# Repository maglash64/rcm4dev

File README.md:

# RCM4DEV
A Raspberry Pi CM4 Dev Board with HDMI outputs, 4 lane MIPI DSI output for 10.1 inch LCD panel with CTP touch, 4 lane MIPI CSI for camera and USB type-C.
Terminal Block for power in 6 - 17V DC.

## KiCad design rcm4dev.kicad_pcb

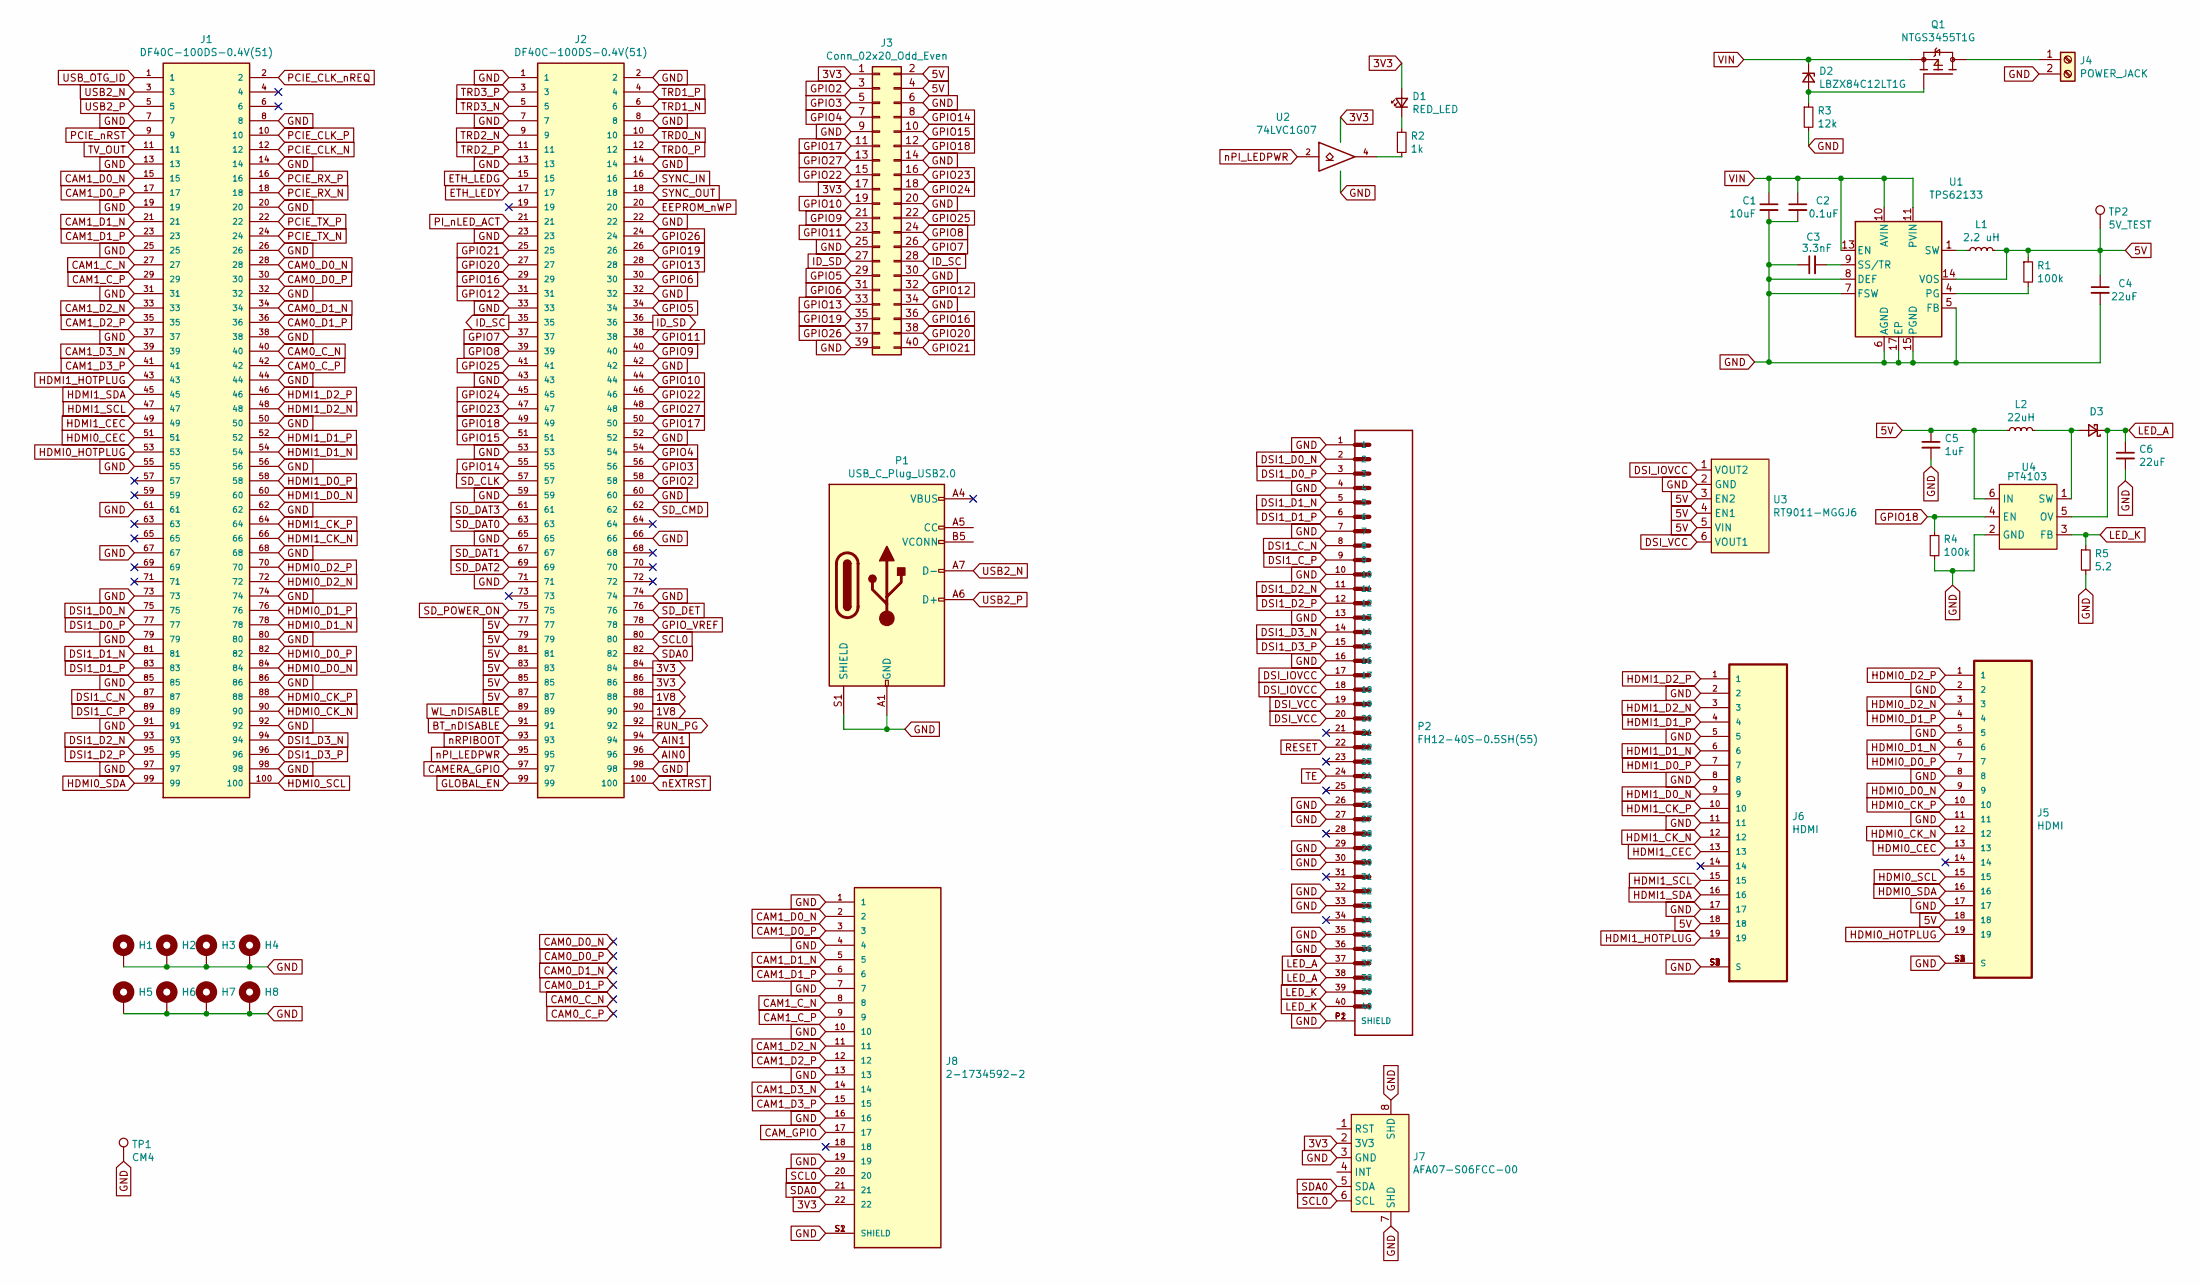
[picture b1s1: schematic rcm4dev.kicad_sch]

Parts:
C1: 10uF; C_1210_3225Metric
C2: 0.1uF; C_0603_1608Metric
C3: 3.3nF; C_0603_1608Metric
C4: 22uF; C_0805_2012Metric
C5: 1uF; C_0603_1608Metric
C6: 22uF; C_0603_1608Metric
D1: RED_LED; LED_0805_2012Metric
D2: LBZX84C12LT1G; SOT-23
D3: D_1206_3216Metric
H1, H2, H3, H4, H5, H6, H7, H8: MountingHole_Pad; MountingHole_2.7mm_M2.5_Pad_Via
J1, J2: DF40C-100DS-0.4V(51); HRS_DF40C-100DS-0.4V(51)
J3: Conn_02x20_Odd_Even; PinHeader_2x20_P2.54mm_Vertical
J4: POWER_JACK; TerminalBlock_Phoenix_MKDS-3-2-5.08_1x02_P5.08mm_Horizontal
J5, J6: HDMI; TE_1827059-3; PARTREV E
J7: AFA07-S06FCC-00
J8: 2-1734592-2; TE_2-1734592-2; PARTREV C
L1: 2.2 uH; L_Vishay_IFSC-1515AH_4x4x1.8mm
L2: 22uH; L_1210_3225Metric
P1: USB_C_Plug_USB2.0; USB_C_Receptacle_HRO_TYPE-C-31-M-12
P2: FH12-40S-0.5SH(55); HRS_FH12-40S-0.5SH(55)
Q1: NTGS3455T1G; SOP95P275X110-6N; PARTREV P
R1: 100k; R_1206_3216Metric
R2: 1k; R_1206_3216Metric
R3: 12k; R_1206_3216Metric
R4: 100k; R_0603_1608Metric
R5: 5.2; R_0603_1608Metric
TP1: CM4; TestPoint_Pad_1.0x1.0mm
TP2: 5V_TEST; TestPoint_Pad_D1.5mm
U1: TPS62133; VQFN-16-1EP_3x3mm_P0.5mm_EP1.68x1.68mm_ThermalVias
U2: 74LVC1G07; SOT-353_SC-70-5
U3: RT9011-MGGJ6; TSOT-23-6
U4: PT4103; TSOT-23-6

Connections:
1V8: J2.88, J2.90
3V3: D1.2 (A), J2.84, J2.86, J3.1, J3.17, J7.2 (3V3), J8.22, U2.5 (VCC)
5V: C4.1, C5.1, J2.77, J2.79, J2.81, J2.83, J2.85, J2.87, J3.2, J3.4, J5.18, J6.18, L1.2, L2.1, R1.1, TP2.1, U1.14 (VOS), U3.3 (EN2), U3.4 (EN1), U3.5 (VIN), U4.6 (IN)
AIN0: J2.96
AIN1: J2.94
BT_nDISABLE: J2.91
CAM0_C_N: J1.40
CAM0_C_P: J1.42
CAM0_D0_N: J1.28
CAM0_D0_P: J1.30
CAM0_D1_N: J1.34
CAM0_D1_P: J1.36
CAM1_C_N: J1.27, J8.8
CAM1_C_P: J1.29, J8.9
CAM1_D0_N: J1.15, J8.2
CAM1_D0_P: J1.17, J8.3
CAM1_D1_N: J1.21, J8.5
CAM1_D1_P: J1.23, J8.6
CAM1_D2_N: J1.33, J8.11
CAM1_D2_P: J1.35, J8.12
CAM1_D3_N: J1.39, J8.14
CAM1_D3_P: J1.41, J8.15
CAMERA_GPIO: J2.97
CAM_GPIO: J8.17
DSI1_C_N: J1.87, P2.8
DSI1_C_P: J1.89, P2.9
DSI1_D0_N: J1.75, P2.2
DSI1_D0_P: J1.77, P2.3
DSI1_D1_N: J1.81, P2.5
DSI1_D1_P: J1.83, P2.6
DSI1_D2_N: J1.93, P2.11
DSI1_D2_P: J1.95, P2.12
DSI1_D3_N: J1.94, P2.14
DSI1_D3_P: J1.96, P2.15
DSI_IOVCC: P2.17, P2.18, U3.1 (VOUT2)
DSI_VCC: P2.19, P2.20, U3.6 (VOUT1)
EEPROM_nWP: J2.20
ETH_LEDG: J2.15
ETH_LEDY: J2.17
GLOBAL_EN: J2.99
GND: C1.2, C2.2, C3.1, C4.2, C5.2, C6.2, H1.1, H2.1, H3.1, H4.1, H5.1, H6.1, H7.1, H8.1, J1.7, J1.8, J1.13, J1.14, J1.19, J1.20, J1.25, J1.26, J1.31, J1.32, J1.37, J1.38, J1.44, J1.50, J1.55, J1.56, J1.61, J1.62, J1.67, J1.68, J1.73, J1.74, J1.79, J1.80, J1.85, J1.86, J1.91, J1.92, J1.97, J1.98, J2.1, J2.2, J2.7, J2.8, J2.13, J2.14, J2.22, J2.23, J2.32, J2.33, J2.42, J2.43, J2.52, J2.53, J2.59, J2.60, J2.65, J2.66, J2.71, J2.74, J2.98, J3.6, J3.9, J3.14, J3.20, J3.25, J3.30, J3.34, J3.39, J4.2, J5.2, J5.5, J5.8, J5.11, J5.17, J5.S1 (S), J5.S2 (S), J5.S3 (S), J5.S4 (S), J6.2, J6.5, J6.8, J6.11, J6.17, J6.S1 (S), J6.S2 (S), J6.S3 (S), J6.S4 (S), J7.3 (GND), J7.7 (SHD), J7.8 (SHD), J8.1, J8.4, J8.7, J8.10, J8.13, J8.16, J8.19, J8.S1 (SHIELD), J8.S2 (SHIELD), P1.A1 (GND), P1.A12 (GND), P1.B1 (GND), P1.B12 (GND), P1.S1 (SHIELD), P2.1, P2.4, P2.7, P2.10, P2.13, P2.16, P2.26, P2.27, P2.29, P2.30, P2.32, P2.33, P2.35, P2.36, P2.P1 (SHIELD), P2.P2 (SHIELD), R3.2, R4.2, R5.2, TP1.1, U1.5 (FB), U1.6 (AGND), U1.7 (FSW), U1.8 (DEF), U1.15 (PGND), U1.16 (PGND), U1.17 (EP), U2.3 (GND), U3.2 (GND), U4.2 (GND)
GPIO2: J2.58, J3.3
GPIO3: J2.56, J3.5
GPIO4: J2.54, J3.7
GPIO5: J2.34, J3.29
GPIO6: J2.30, J3.31
GPIO7: J2.37, J3.26
GPIO8: J2.39, J3.24
GPIO9: J2.40, J3.21
GPIO10: J2.44, J3.19
GPIO11: J2.38, J3.23
GPIO12: J2.31, J3.32
GPIO13: J2.28, J3.33
GPIO14: J2.55, J3.8
GPIO15: J2.51, J3.10
GPIO16: J2.29, J3.36
GPIO17: J2.50, J3.11
GPIO18: J2.49, J3.12, R4.1, U4.4 (EN)
GPIO19: J2.26, J3.35
GPIO20: J2.27, J3.38
GPIO21: J2.25, J3.40
GPIO22: J2.46, J3.15
GPIO23: J2.47, J3.16
GPIO24: J2.45, J3.18
GPIO25: J2.41, J3.22
GPIO26: J2.24, J3.37
GPIO27: J2.48, J3.13
GPIO_VREF: J2.78
HDMI0_CEC: J1.51, J5.13
HDMI0_CK_N: J1.90, J5.12
HDMI0_CK_P: J1.88, J5.10
HDMI0_D0_N: J1.84, J5.9
HDMI0_D0_P: J1.82, J5.7
HDMI0_D1_N: J1.78, J5.6
HDMI0_D1_P: J1.76, J5.4
HDMI0_D2_N: J1.72, J5.3
HDMI0_D2_P: J1.70, J5.1
HDMI0_HOTPLUG: J1.53, J5.19
HDMI0_SCL: J1.100, J5.15
HDMI0_SDA: J1.99, J5.16
HDMI1_CEC: J1.49, J6.13
HDMI1_CK_N: J1.66, J6.12
HDMI1_CK_P: J1.64, J6.10
HDMI1_D0_N: J1.60, J6.9
HDMI1_D0_P: J1.58, J6.7
HDMI1_D1_N: J1.54, J6.6
HDMI1_D1_P: J1.52, J6.4
HDMI1_D2_N: J1.48, J6.3
HDMI1_D2_P: J1.46, J6.1
HDMI1_HOTPLUG: J1.43, J6.19
HDMI1_SCL: J1.47, J6.15
HDMI1_SDA: J1.45, J6.16
ID_SC: J2.35, J3.28
ID_SD: J2.36, J3.27
LED_A: C6.1, D3.1 (K), P2.37, P2.38, U4.5 (OV)
LED_K: P2.39, P2.40, R5.1, U4.3 (FB)
unnamed: C3.2, U1.9 (SS/TR)
unnamed: D1.1 (K), R2.1
unnamed: D2.2 (A), Q1.3, R3.1
unnamed: D3.2 (A), L2.2, U4.1 (SW)
unnamed: J4.1, Q1.1, Q1.2, Q1.5, Q1.6
unnamed: L1.1, U1.1 (SW), U1.2 (SW), U1.3 (SW)
unnamed: P1.A4 (VBUS), P1.A9 (VBUS), P1.B4 (VBUS), P1.B9 (VBUS)
unnamed: R1.2, U1.4 (PG)
unnamed: R2.2, U2.4
PCIE_CLK_N: J1.12
PCIE_CLK_P: J1.10
PCIE_CLK_nREQ: J1.2
PCIE_RX_N: J1.18
PCIE_RX_P: J1.16
PCIE_TX_N: J1.24
PCIE_TX_P: J1.22
PCIE_nRST: J1.9
PI_nLED_ACT: J2.21
RESET: P2.22
RUN_PG: J2.92
SCL0: J2.80, J7.6 (SCL), J8.20
SDA0: J2.82, J7.5 (SDA), J8.21
SD_CLK: J2.57
SD_CMD: J2.62
SD_DAT0: J2.63
SD_DAT1: J2.67
SD_DAT2: J2.69
SD_DAT3: J2.61
SD_DET: J2.76
SD_POWER_ON: J2.75
SYNC_IN: J2.16
SYNC_OUT: J2.18
TE: P2.24
TRD0_N: J2.10
TRD0_P: J2.12
TRD1_N: J2.6
TRD1_P: J2.4
TRD2_N: J2.9
TRD2_P: J2.11
TRD3_N: J2.5
TRD3_P: J2.3
TV_OUT: J1.11
USB2_N: J1.3, P1.A7 (D-)
USB2_P: J1.5, P1.A6 (D+)
USB_OTG_ID: J1.1
VIN: C1.1, C2.1, D2.1 (K), Q1.4, U1.10 (AVIN), U1.11 (PVIN), U1.12 (PVIN), U1.13 (EN)
WL_nDISABLE: J2.89
nEXTRST: J2.100
nPI_LEDPWR: J2.95, U2.2
nRPIBOOT: J2.93

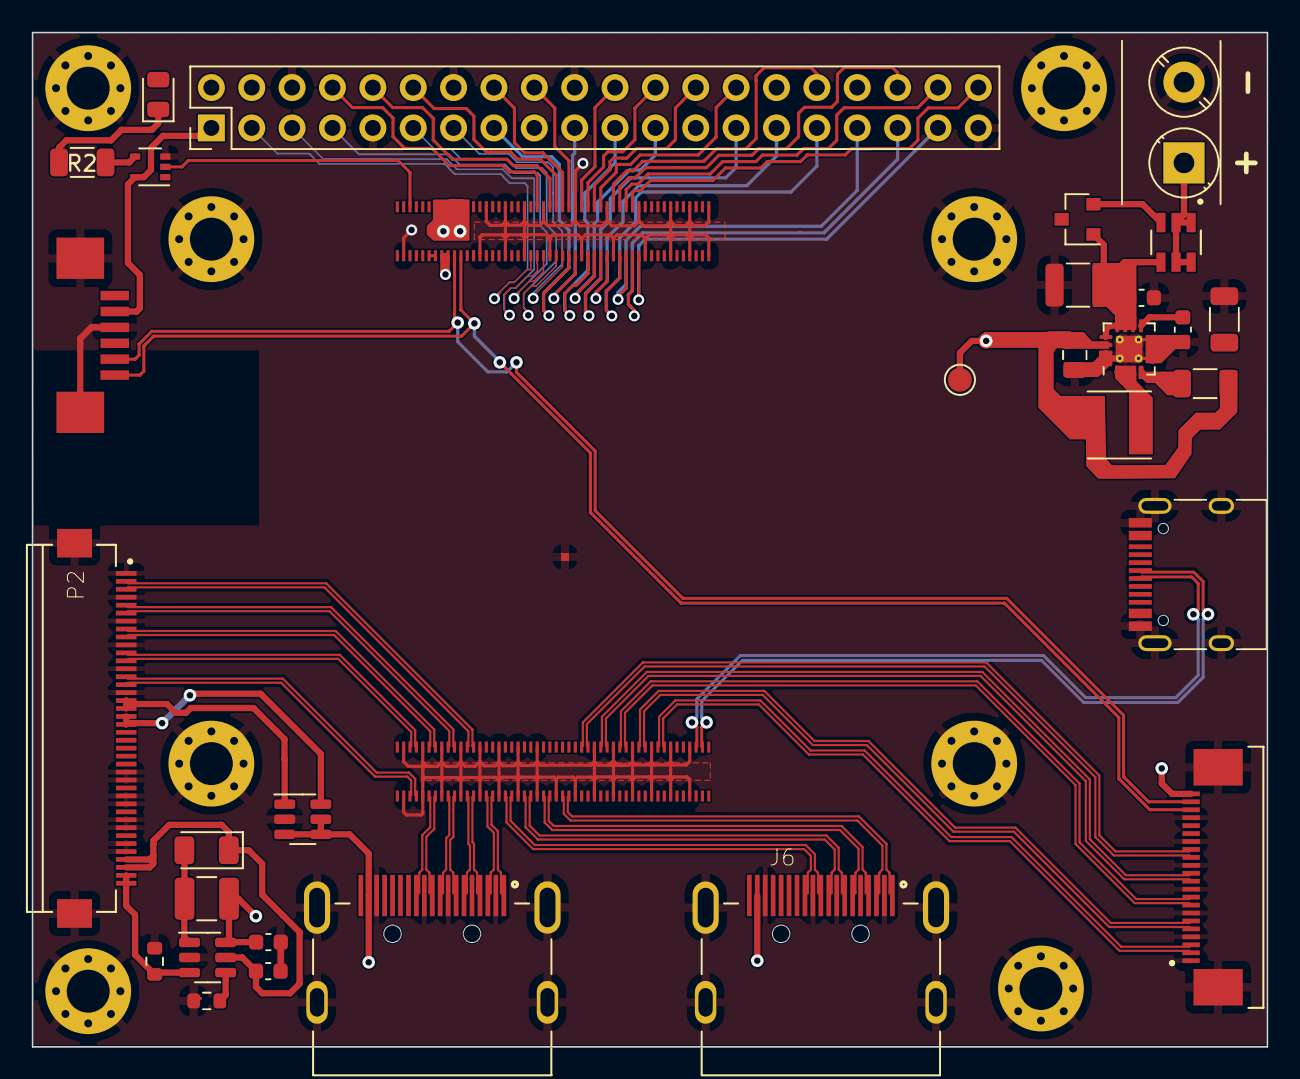
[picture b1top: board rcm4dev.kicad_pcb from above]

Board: 4 copper layers, 77.7 x 63.8 mm, 41 parts (0 on the bottom side), 95 nets.

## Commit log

2020-12-07 uploaded
